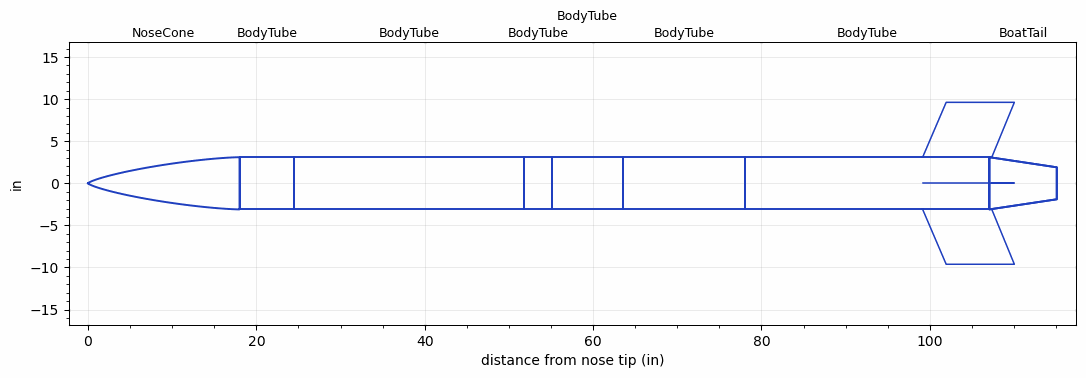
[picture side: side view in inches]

<RASAeroDocument>
 <FileVersion>2</FileVersion>
 <RocketDesign>
  <NoseCone>
   <Length>18</Length>
   <Diameter>6.2</Diameter>
   <Shape>Von Karman Ogive</Shape>
   <Location>0</Location>
  </NoseCone>
  <BodyTube>
   <Length>6.5</Length>
   <Diameter>6.2</Diameter>
   <Location>18</Location>
  </BodyTube>
  <BodyTube>
   <Length>27.3359</Length>
   <Diameter>6.2</Diameter>
   <Location>24.5</Location>
  </BodyTube>
  <BodyTube>
   <Length>3.25</Length>
   <Diameter>6.2</Diameter>
   <Location>51.8359</Location>
  </BodyTube>
  <BodyTube>
   <Length>8.5</Length>
   <Diameter>6.2</Diameter>
   <Location>55.0859</Location>
  </BodyTube>
  <BodyTube>
   <Length>14.5</Length>
   <Diameter>6.2</Diameter>
   <Location>63.5859</Location>
  </BodyTube>
  <BodyTube>
   <Length>28.9999</Length>
   <Diameter>6.2</Diameter>
   <RailGuideDiameter>0.621</RailGuideDiameter>
   <RailGuideHeight>0.684</RailGuideHeight>
   <Location>78.0859</Location>
   <BoattailLength>8</BoattailLength>
   <BoattailRearDiameter>3.8</BoattailRearDiameter>
   <Overhang>0.2790003</Overhang>
   <Fin>
    <Count>4</Count>
    <Chord>8.213</Chord>
    <Span>6.52</Span>
    <SweepDistance>2.795</SweepDistance>
    <TipChord>8.1</TipChord>
    <Thickness>0.2</Thickness>
    <Location>7.934</Location>
    <AirfoilSection>Rounded</AirfoilSection>
   </Fin>
  </BodyTube>
  <BoatTail>
   <Length>8</Length>
   <Diameter>6.2</Diameter>
   <RearDiameter>3.8</RearDiameter>
   <Location>107.0858</Location>
  </BoatTail>
  <Surface>Sheet Metal</Surface>
  <ModifiedBarrowman>False</ModifiedBarrowman>
  <Turbulence>False</Turbulence>
  <UseBooster1>False</UseBooster1>
  <UseBooster2>False</UseBooster2>
 </RocketDesign>
 <LaunchSite>
  <Altitude>2871</Altitude>
  <Pressure>28.9938</Pressure>
  <RodAngle>6</RodAngle>
  <RodLength>154.9997</RodLength>
  <Temperature>86</Temperature>
  <WindSpeed>1.5882</WindSpeed>
 </LaunchSite>
 <Recovery>
  <Altitude1>1476</Altitude1>
  <Altitude2>656.168</Altitude2>
  <DeviceType1>Parachute</DeviceType1>
  <DeviceType2>Parachute</DeviceType2>
  <Event1>True</Event1>
  <Event2>True</Event2>
  <Size1>95.9998</Size1>
  <Size2>35.9999</Size2>
  <EventType1>Altitude</EventType1>
  <EventType2>Apogee</EventType2>
  <CD1>1.35</CD1>
  <CD2>0</CD2>
 </Recovery>
 <SimulationList>
  <Simulation>
   <SustainerLaunchWt>59.6956</SustainerLaunchWt>
   <SustainerCG>68.6906</SustainerCG>
   <SustainerIgnitionDelay>0</SustainerIgnitionDelay>
   <Booster1SeparationDelay>0</Booster1SeparationDelay>
   <Booster1IgnitionDelay>0</Booster1IgnitionDelay>
   <IncludeBooster1>False</IncludeBooster1>
   <Booster2Delay>0</Booster2Delay>
   <IncludeBooster2>False</IncludeBooster2>
  </Simulation>
 </SimulationList>
</RASAeroDocument>
